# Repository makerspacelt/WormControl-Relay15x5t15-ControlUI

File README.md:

---

WormControl Relay Control and User Interface boards

NOTE: This is only a prototype now, so things might not work and everything might change 

Basic target features:

* Compatibility with esphome and Home Assistant

Dev NOTE: before commit, run `./kibot.sh` to regenerate documentation, bom, gerbers and other assets.

* [schematics.pdf](gen/schematics.pdf)
* [pcb.pdf with dimensions](gen/pcb.pdf)
* [ibom.html](gen/single/ibom.html)

---

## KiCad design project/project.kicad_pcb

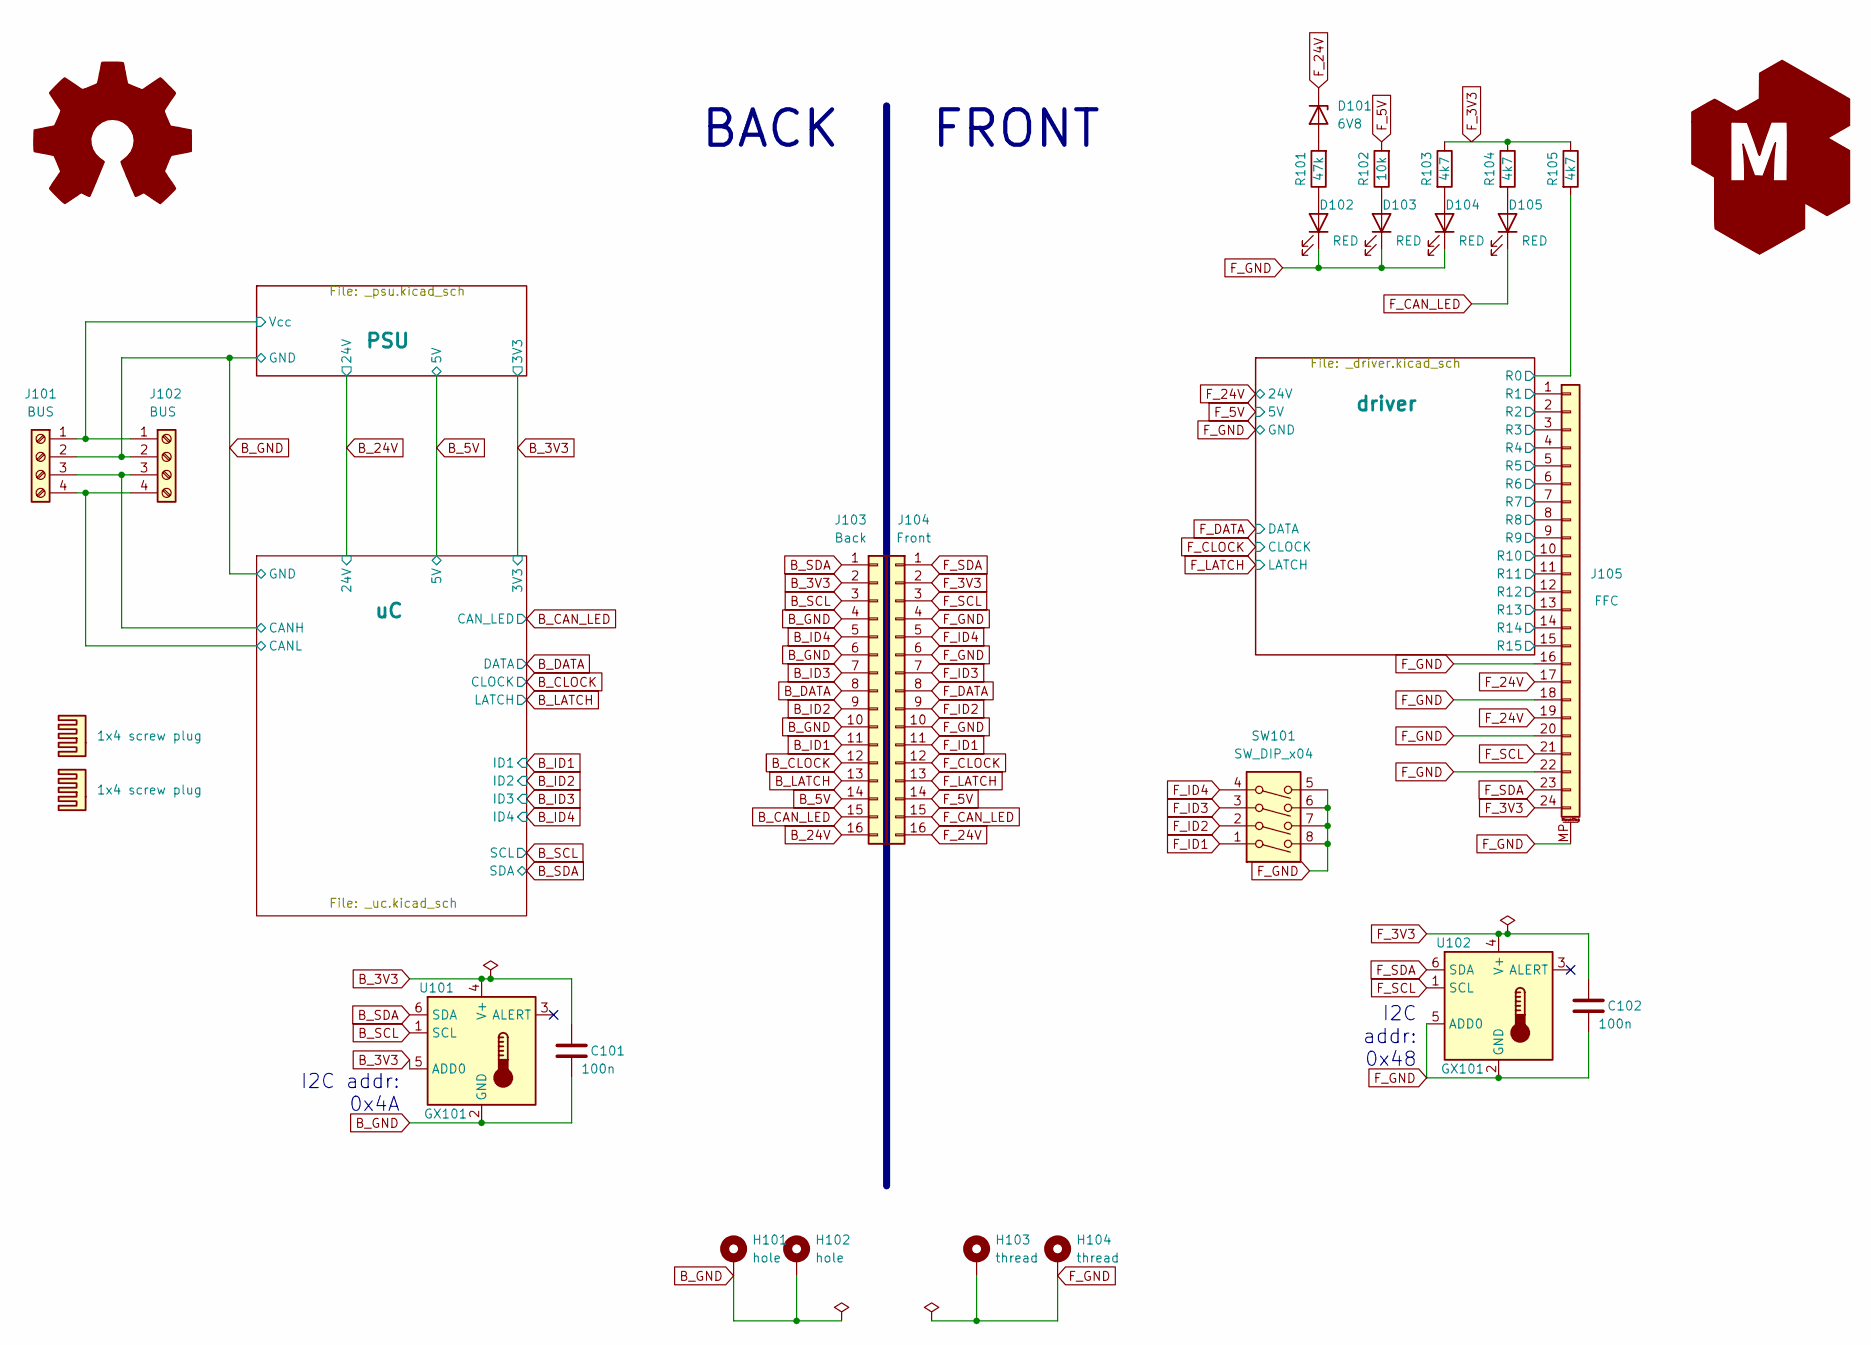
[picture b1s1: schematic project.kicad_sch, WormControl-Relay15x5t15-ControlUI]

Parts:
BOM101, BOM102: 1x4 screw plug; jlc-part-type E
C101, C102: 100n; C_0805_2012Metric_Pad1.18x1.45mm_HandSolder; jlc-part-type B
D101: 6V8; D_SOD-323_HandSoldering; jlc-part-type E
D102, D103, D104, D105: RED; LED_1206_3216Metric_ReverseMount; jlc-part-type E
G101: Logo_Open_Hardware_Large; OSHW-Symbol_6.7x6mm_SilkScreen
G102: LOGO_KMS; logo_kms_small_silkscreen
H101, H102: hole; MountingHole_3.2mm_M3_Pad_Via
H103, H104: thread; post_m3x12.5mm; lcsc# C30182781
J101, J102: BUS; PhoenixContact_MCV_1,5_4-G-3.5_1x04_P3.50mm_Vertical; jlc-part-type E
J103: Back; PinSocket_2x08_P2.54mm_Vertical_SMD; lcsc# C3975153
J104: Front; PinHeader_2x08_P2.54mm_Vertical_SMD; lcsc# C5160782
J105: FFC; AFC11-S24ICC-00; jlc-part-type E
R101: 47k; R_0805_2012Metric_Pad1.20x1.40mm_HandSolder; jlc-part-type B
R102: 10k; R_0805_2012Metric_Pad1.20x1.40mm_HandSolder; jlc-part-type B
R103, R104, R105: 4k7; R_0805_2012Metric_Pad1.20x1.40mm_HandSolder; jlc-part-type B
SW101: SW_DIP_x04; SW_DIP_SPSTx04_Slide_6.2x11.16mm_P2.54mm; lcsc# C976366
U101, U102: GX101; SOT-23-6; jlc-part-type E

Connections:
/PSU/Vcc: J101.1, J102.1; also elsewhere on the board
/driver/R0: R105.2; also elsewhere on the board
/driver/R1: J105.1; also elsewhere on the board
/driver/R2: J105.2; also elsewhere on the board
/driver/R3: J105.3; also elsewhere on the board
/driver/R4: J105.4; also elsewhere on the board
/driver/R5: J105.5; also elsewhere on the board
/driver/R6: J105.6; also elsewhere on the board
/driver/R7: J105.7; also elsewhere on the board
/driver/R8: J105.8; also elsewhere on the board
/driver/R9: J105.9; also elsewhere on the board
/driver/R10: J105.10; also elsewhere on the board
/driver/R11: J105.11; also elsewhere on the board
/driver/R12: J105.12; also elsewhere on the board
/driver/R13: J105.13; also elsewhere on the board
/driver/R14: J105.14; also elsewhere on the board
/driver/R15: J105.15; also elsewhere on the board
/uC/CANH: J101.3, J102.3; also elsewhere on the board
/uC/CANL: J101.4, J102.4; also elsewhere on the board
B_3V3: C101.1, J103.2, U101.4 (V+), U101.5 (ADD0); also elsewhere on the board
B_5V: J103.14; also elsewhere on the board
B_24V: J103.16; also elsewhere on the board
B_CAN_LED: J103.15; also elsewhere on the board
B_CLOCK: J103.12; also elsewhere on the board
B_DATA: J103.8; also elsewhere on the board
B_GND: C101.2, H101.1, H102.1, J101.2, J102.2, J103.4, J103.6, J103.10, U101.2 (GND); also elsewhere on the board
B_ID1: J103.11; also elsewhere on the board
B_ID2: J103.9; also elsewhere on the board
B_ID3: J103.7; also elsewhere on the board
B_ID4: J103.5; also elsewhere on the board
B_LATCH: J103.13; also elsewhere on the board
B_SCL: J103.3, U101.1 (SCL); also elsewhere on the board
B_SDA: J103.1, U101.6 (SDA); also elsewhere on the board
F_3V3: C102.1, J104.2, J105.24, R103.1, R104.1, R105.1, U102.4 (V+)
F_5V: J104.14, R102.2; also elsewhere on the board
F_24V: D101.1 (K), J104.16, J105.17, J105.19; also elsewhere on the board
F_CAN_LED: D105.1 (K), J104.15
F_CLOCK: J104.12; also elsewhere on the board
F_DATA: J104.8; also elsewhere on the board
F_GND: C102.2, D102.1 (K), D103.1 (K), D104.1 (K), H103.1, H104.1, J104.4, J104.6, J104.10, J105.16, J105.18, J105.20, J105.22, J105.MP (MountPin), SW101.5, SW101.6, SW101.7, SW101.8, U102.2 (GND), U102.5 (ADD0); also elsewhere on the board
F_ID1: J104.11, SW101.1
F_ID2: J104.9, SW101.2
F_ID3: J104.7, SW101.3
F_ID4: J104.5, SW101.4
F_LATCH: J104.13; also elsewhere on the board
F_SCL: J104.3, J105.21, U102.1 (SCL)
F_SDA: J104.1, J105.23, U102.6 (SDA)
unnamed: D101.2 (A), R101.2
unnamed: D102.2 (A), R101.1
unnamed: D103.2 (A), R102.1
unnamed: D104.2 (A), R103.2
unnamed: D105.2 (A), R104.2

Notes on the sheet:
I2C addr: 0x48
FRONT
I2C addr: 0x4A
BACK

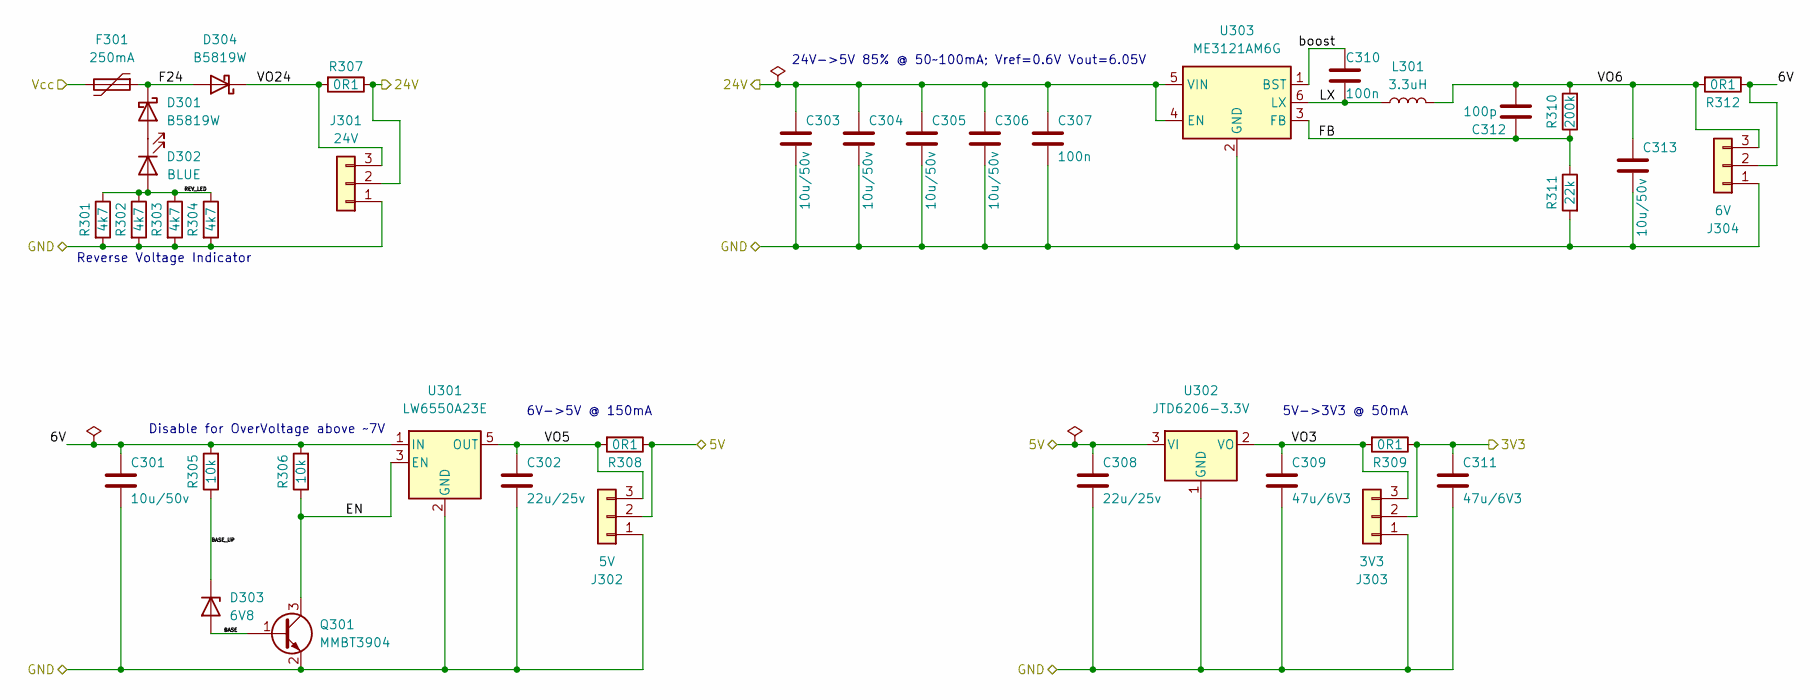
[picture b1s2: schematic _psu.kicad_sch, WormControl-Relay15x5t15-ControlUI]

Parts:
C301, C303, C304, C305, C306, C313: 10u/50v; C_0805_2012Metric_Pad1.18x1.45mm_HandSolder; jlc-part-type B
C302, C308: 22u/25v; C_0805_2012Metric_Pad1.18x1.45mm_HandSolder; jlc-part-type B
C307, C310: 100n; C_0805_2012Metric_Pad1.18x1.45mm_HandSolder; jlc-part-type B
C309, C311: 47u/6V3; C_0805_2012Metric_Pad1.18x1.45mm_HandSolder; jlc-part-type B
C312: 100p; C_0805_2012Metric_Pad1.18x1.45mm_HandSolder; jlc-part-type B
D301, D304: B5819W; D_SOD-123; jlc-part-type B
D302: BLUE; LED_0805_2012Metric_Pad1.15x1.40mm_HandSolder; jlc-part-type B
D303: 6V8; D_SOD-323_HandSoldering; jlc-part-type E
F301: 250mA; Fuse_0805_2012Metric_Pad1.15x1.40mm_HandSolder; lcsc# C22378353
J301: 24V; PinHeader_1x03_P2.54mm_Vertical
J302: 5V; PinHeader_1x03_P2.54mm_Vertical
J303: 3V3; PinHeader_1x03_P2.54mm_Vertical
J304: 6V; PinHeader_1x03_P2.54mm_Vertical
L301: 3.3uH; L_1008_2520Metric_Pad1.43x2.20mm_HandSolder; jlc-part-type E
Q301: MMBT3904; SOT-23; jlc-part-type B
R301, R302, R303, R304: 4k7; R_0805_2012Metric_Pad1.20x1.40mm_HandSolder; jlc-part-type B
R305, R306: 10k; R_0805_2012Metric_Pad1.20x1.40mm_HandSolder; jlc-part-type B
R307, R308, R309, R312: 0R1; R_0805_2012Metric_Pad1.20x1.40mm_HandSolder; jlc-part-type E
R310: 200k; R_0805_2012Metric_Pad1.20x1.40mm_HandSolder; jlc-part-type B
R311: 22k; R_0805_2012Metric_Pad1.20x1.40mm_HandSolder; jlc-part-type B
U301: LW6550A23E; SOT-23-5; jlc-part-type E
U302: JTD6206-3.3V; SOT-23; jlc-part-type B
U303: ME3121AM6G; SOT-23-6; jlc-part-type E

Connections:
/PSU/6V: C301.1, J304.2, R305.2, R306.2, R312.1, U301.1 (IN)
/PSU/BASE: D303.2 (A), Q301.1 (B)
/PSU/BASE_UP: D303.1 (K), R305.1
/PSU/EN: Q301.3 (C), R306.1, U301.3 (EN)
/PSU/F24: D301.1 (K), D304.2 (A), F301.1
/PSU/FB: C312.1, R310.1, R311.1, U303.3 (FB)
/PSU/LX: C310.2, L301.1, U303.6 (LX)
/PSU/REV_LED: D302.2 (A), R301.1, R302.1, R303.1, R304.1
/PSU/VO3: C309.1, J303.3, R309.2, U302.2 (VO)
/PSU/VO5: C302.1, J302.3, R308.2, U301.5 (OUT)
/PSU/VO6: C312.2, C313.1, J304.3, L301.2, R310.2, R312.2
/PSU/VO24: D304.1 (K), J301.3, R307.2
/PSU/Vcc: F301.2; also elsewhere on the board
/PSU/boost: C310.1, U303.1 (BST)
B_3V3: C311.1, J303.2, R309.1; also elsewhere on the board
B_5V: C308.1, J302.2, R308.1, U302.3 (VI); also elsewhere on the board
B_24V: C303.1, C304.1, C305.1, C306.1, C307.1, J301.2, R307.1, U303.4 (EN), U303.5 (VIN); also elsewhere on the board
B_GND: C301.2, C302.2, C303.2, C304.2, C305.2, C306.2, C307.2, C308.2, C309.2, C311.2, C313.2, J301.1, J302.1, J303.1, J304.1, Q301.2 (E), R301.2, R302.2, R303.2, R304.2, R311.2, U301.2 (GND), U302.1 (GND), U303.2 (GND); also elsewhere on the board
unnamed: D301.2 (A), D302.1 (K)

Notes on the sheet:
24V->5V 85% @ 50~100mA; Vref=0.6V Vout=6.05V
5V->3V3 @ 50mA
Reverse Voltage Indicator
6V->5V @ 150mA
Disable for OverVoltage above ~7V

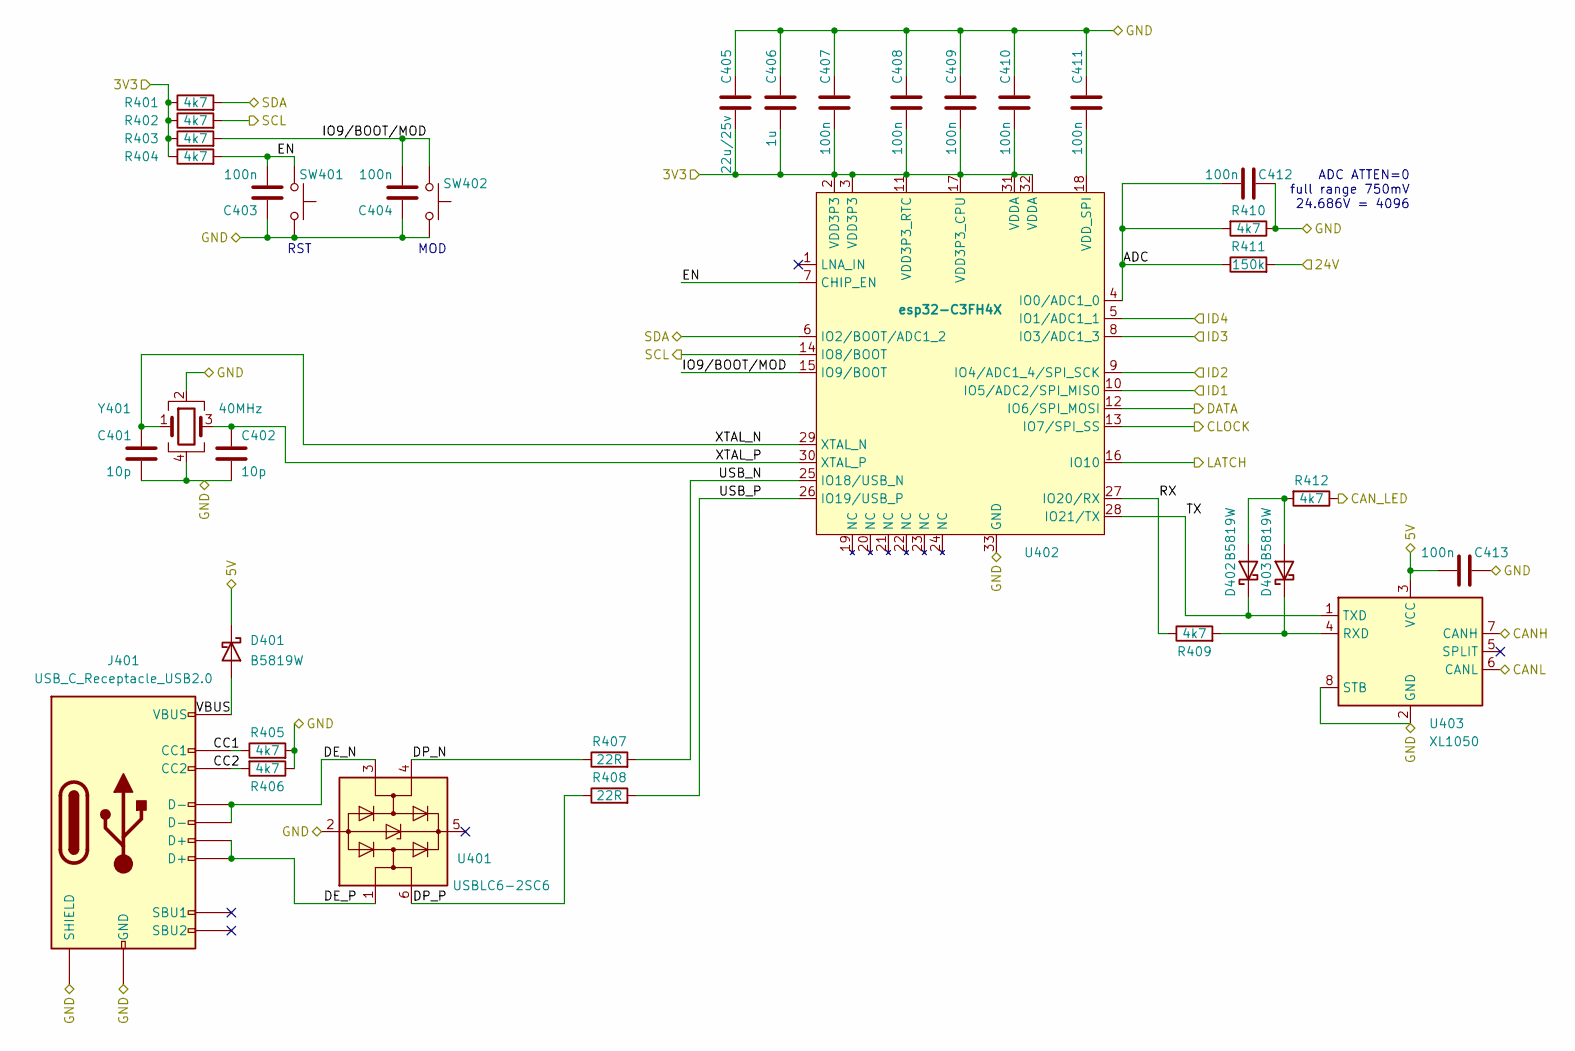
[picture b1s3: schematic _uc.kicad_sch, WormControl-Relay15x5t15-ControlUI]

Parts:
C401, C402: 10p; C_0805_2012Metric_Pad1.18x1.45mm_HandSolder; jlc-part-type B
C403, C404, C407, C408, C409, C410, C411, C412, C413: 100n; C_0805_2012Metric_Pad1.18x1.45mm_HandSolder; jlc-part-type B
C405: 22u/25v; C_0805_2012Metric_Pad1.18x1.45mm_HandSolder; jlc-part-type B
C406: 1u; C_0805_2012Metric_Pad1.18x1.45mm_HandSolder; jlc-part-type B
D401, D402, D403: B5819W; D_SOD-123; jlc-part-type B
J401: USB_C_Receptacle_USB2.0; USB_C_Receptacle_G-Switch_GT-USB-7082G; jlc-part-type E
R401, R402, R403, R404, R405, R406, R409, R410, R412: 4k7; R_0805_2012Metric_Pad1.20x1.40mm_HandSolder; jlc-part-type B
R407, R408: 22R; R_0805_2012Metric_Pad1.20x1.40mm_HandSolder; jlc-part-type B
R411: 150k; R_0805_2012Metric_Pad1.20x1.40mm_HandSolder; jlc-part-type B
SW401, SW402: 15mm; SW_SPST_15; jlc-part-type E
U401: USBLC6-2SC6; SOT-23-6; jlc-part-type E
U402: esp32-C3FH4X; QFN-32-1EP_5x5mm_P0.5mm_EP3.65x3.65mm; jlc-part-type E
U403: XL1050; SOIC-8_3.9x4.9mm_P1.27mm; jlc-part-type E
Y401: 40MHz; Crystal_SMD_3225-4Pin_3.2x2.5mm; jlc-part-type E

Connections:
/uC/ADC: C412.1, R410.2, R411.1, U402.4 (IO0/ADC1_0)
/uC/CANH: U403.7 (CANH); also elsewhere on the board
/uC/CANL: U403.6 (CANL); also elsewhere on the board
/uC/CC1: J401.A5 (CC1), R405.1
/uC/CC2: J401.B5 (CC2), R406.2
/uC/DE_N: J401.A7 (D-), J401.B7 (D-), U401.3 (I/O2)
/uC/DE_P: J401.A6 (D+), J401.B6 (D+), U401.1 (I/O1)
/uC/DP_N: R407.1, U401.4 (I/O2)
/uC/DP_P: R408.1, U401.6 (I/O1)
/uC/EN: C403.2, R404.2, SW401.1, U402.7 (CHIP_EN)
/uC/IO9/BOOT/MOD: C404.2, R403.2, SW402.1, U402.15 (IO9/BOOT)
/uC/RX: R409.1, U402.27 (IO20/RX)
/uC/TX: D402.1 (K), U402.28 (IO21/TX), U403.1 (TXD)
/uC/USB_N: R407.2, U402.25 (IO18/USB_N)
/uC/USB_P: R408.2, U402.26 (IO19/USB_P)
/uC/VBUS: D401.2 (A), J401.A4 (VBUS), J401.A9 (VBUS), J401.B4 (VBUS), J401.B9 (VBUS)
/uC/XTAL_N: C401.1, U402.29 (XTAL_N), Y401.1
/uC/XTAL_P: C402.1, U402.30 (XTAL_P), Y401.3
B_3V3: C405.2, C406.2, C407.1, C408.1, C409.1, C410.1, R401.1, R402.1, R403.1, R404.1, U402.2 (VDD3P3), U402.3 (VDD3P3), U402.11 (VDD3P3_RTC), U402.17 (VDD3P3_CPU), U402.31 (VDDA), U402.32 (VDDA); also elsewhere on the board
B_5V: C413.1, D401.1 (K), U403.3 (VCC); also elsewhere on the board
B_24V: R411.2; also elsewhere on the board
B_CAN_LED: R412.1; also elsewhere on the board
B_CLOCK: U402.13 (IO7/SPI_SS); also elsewhere on the board
B_DATA: U402.12 (IO6/SPI_MOSI); also elsewhere on the board
B_GND: C401.2, C402.2, C403.1, C404.1, C405.1, C406.1, C407.2, C408.2, C409.2, C410.2, C411.2, C412.2, C413.2, J401.A1 (GND), J401.A12 (GND), J401.B1 (GND), J401.B12 (GND), J401.S1 (SHIELD), R405.2, R406.1, R410.1, SW401.2, SW402.2, U401.2 (GND), U402.33 (GND), U403.2 (GND), U403.8 (STB), Y401.2, Y401.4; also elsewhere on the board
B_ID1: U402.10 (IO5/ADC2/SPI_MISO); also elsewhere on the board
B_ID2: U402.9 (IO4/ADC1_4/SPI_SCK); also elsewhere on the board
B_ID3: U402.8 (IO3/ADC1_3); also elsewhere on the board
B_ID4: U402.5 (IO1/ADC1_1); also elsewhere on the board
B_LATCH: U402.16 (IO10); also elsewhere on the board
B_SCL: R402.2, U402.14 (IO8/BOOT); also elsewhere on the board
B_SDA: R401.2, U402.6 (IO2/BOOT/ADC1_2); also elsewhere on the board
unnamed: C411.1, U402.18 (VDD_SPI)
unnamed: D402.2 (A), D403.2 (A), R412.2
unnamed: D403.1 (K), R409.2, U403.4 (RXD)

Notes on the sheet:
RST
ADC ATTEN=0 full range 750mV 24.686V = 4096
MOD

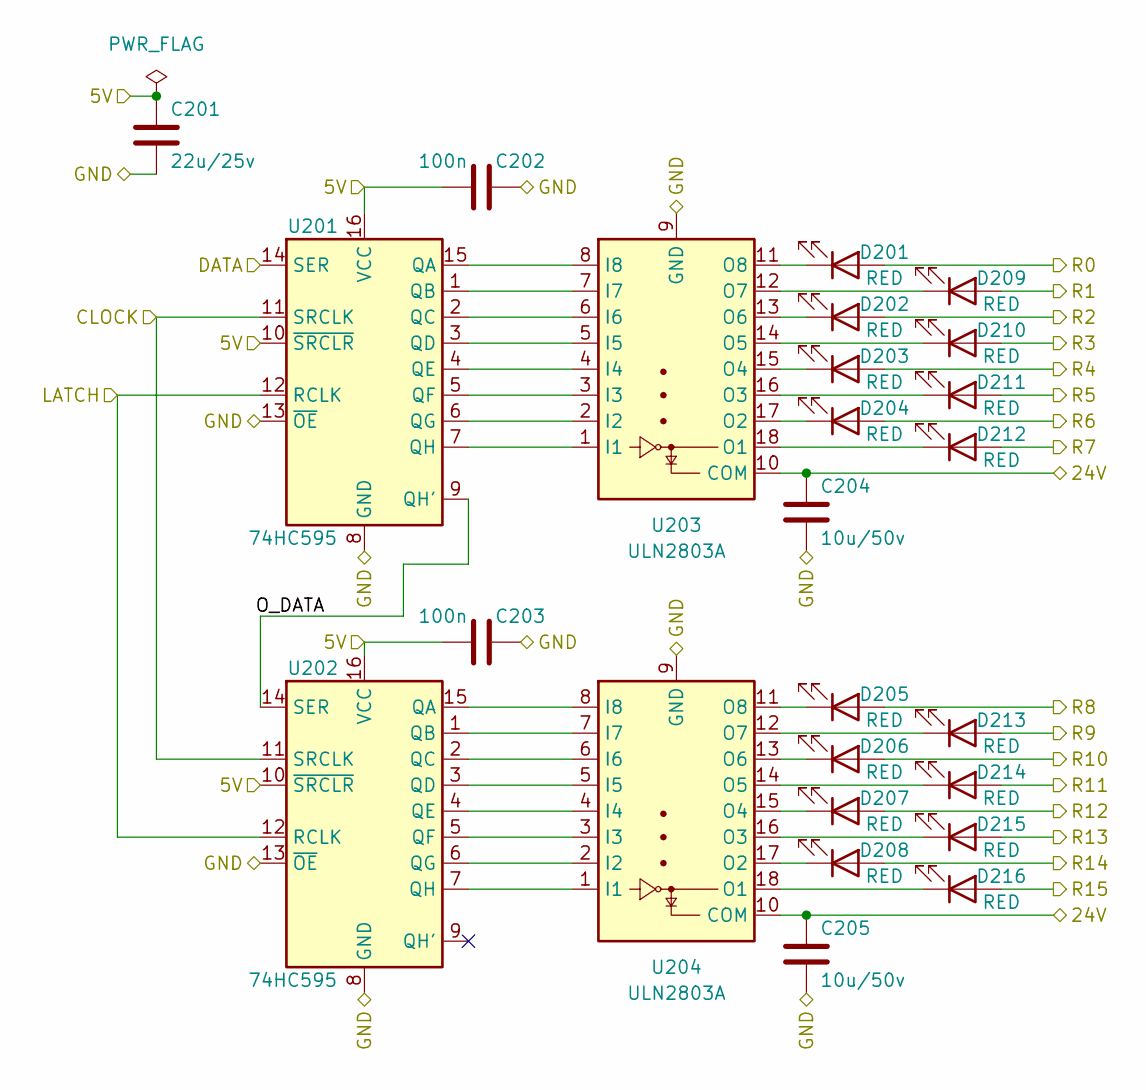
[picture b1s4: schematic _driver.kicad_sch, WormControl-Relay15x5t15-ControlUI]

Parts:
C201: 22u/25v; C_0805_2012Metric_Pad1.18x1.45mm_HandSolder; jlc-part-type B
C202, C203: 100n; C_0805_2012Metric_Pad1.18x1.45mm_HandSolder; jlc-part-type B
C204, C205: 10u/50v; C_0805_2012Metric_Pad1.18x1.45mm_HandSolder; jlc-part-type B
D201, D202, D203, D204, D205, D206, D207, D208, D209, D210, D211, D212, D213, D214, D215, D216: RED; LED_1206_3216Metric_ReverseMount; jlc-part-type E
U201, U202: 74HC595; SOIC-16_3.9x9.9mm_P1.27mm; jlc-part-type B
U203, U204: ULN2803A; SOIC-18W_7.5x11.6mm_P1.27mm; jlc-part-type E

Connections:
/driver/O_DATA: U201.9 (QH'), U202.14 (SER)
/driver/R0: D201.2 (A); also elsewhere on the board
/driver/R1: D209.2 (A); also elsewhere on the board
/driver/R2: D202.2 (A); also elsewhere on the board
/driver/R3: D210.2 (A); also elsewhere on the board
/driver/R4: D203.2 (A); also elsewhere on the board
/driver/R5: D211.2 (A); also elsewhere on the board
/driver/R6: D204.2 (A); also elsewhere on the board
/driver/R7: D212.2 (A); also elsewhere on the board
/driver/R8: D205.2 (A); also elsewhere on the board
/driver/R9: D213.2 (A); also elsewhere on the board
/driver/R10: D206.2 (A); also elsewhere on the board
/driver/R11: D214.2 (A); also elsewhere on the board
/driver/R12: D207.2 (A); also elsewhere on the board
/driver/R13: D215.2 (A); also elsewhere on the board
/driver/R14: D208.2 (A); also elsewhere on the board
/driver/R15: D216.2 (A); also elsewhere on the board
F_5V: C201.1, C202.1, C203.1, U201.10 (~SRCLR), U201.16 (VCC), U202.10 (~SRCLR), U202.16 (VCC); also elsewhere on the board
F_24V: C204.1, C205.1, U203.10 (COM), U204.10 (COM); also elsewhere on the board
F_CLOCK: U201.11 (SRCLK), U202.11 (SRCLK); also elsewhere on the board
F_DATA: U201.14 (SER); also elsewhere on the board
F_GND: C201.2, C202.2, C203.2, C204.2, C205.2, U201.8 (GND), U201.13 (~OE), U202.8 (GND), U202.13 (~OE), U203.9 (GND), U204.9 (GND); also elsewhere on the board
F_LATCH: U201.12 (RCLK), U202.12 (RCLK); also elsewhere on the board
unnamed: D201.1 (K), U203.11 (O8)
unnamed: D202.1 (K), U203.13 (O6)
unnamed: D203.1 (K), U203.15 (O4)
unnamed: D204.1 (K), U203.17 (O2)
unnamed: D205.1 (K), U204.11 (O8)
unnamed: D206.1 (K), U204.13 (O6)
unnamed: D207.1 (K), U204.15 (O4)
unnamed: D208.1 (K), U204.17 (O2)
unnamed: D209.1 (K), U203.12 (O7)
unnamed: D210.1 (K), U203.14 (O5)
unnamed: D211.1 (K), U203.16 (O3)
unnamed: D212.1 (K), U203.18 (O1)
unnamed: D213.1 (K), U204.12 (O7)
unnamed: D214.1 (K), U204.14 (O5)
unnamed: D215.1 (K), U204.16 (O3)
unnamed: D216.1 (K), U204.18 (O1)
unnamed: U201.1 (QB), U203.7 (I7)
unnamed: U201.2 (QC), U203.6 (I6)
unnamed: U201.3 (QD), U203.5 (I5)
unnamed: U201.4 (QE), U203.4 (I4)
unnamed: U201.5 (QF), U203.3 (I3)
unnamed: U201.6 (QG), U203.2 (I2)
unnamed: U201.7 (QH), U203.1 (I1)
unnamed: U201.15 (QA), U203.8 (I8)
unnamed: U202.1 (QB), U204.7 (I7)
unnamed: U202.2 (QC), U204.6 (I6)
unnamed: U202.3 (QD), U204.5 (I5)
unnamed: U202.4 (QE), U204.4 (I4)
unnamed: U202.5 (QF), U204.3 (I3)
unnamed: U202.6 (QG), U204.2 (I2)
unnamed: U202.7 (QH), U204.1 (I1)
unnamed: U202.15 (QA), U204.8 (I8)
